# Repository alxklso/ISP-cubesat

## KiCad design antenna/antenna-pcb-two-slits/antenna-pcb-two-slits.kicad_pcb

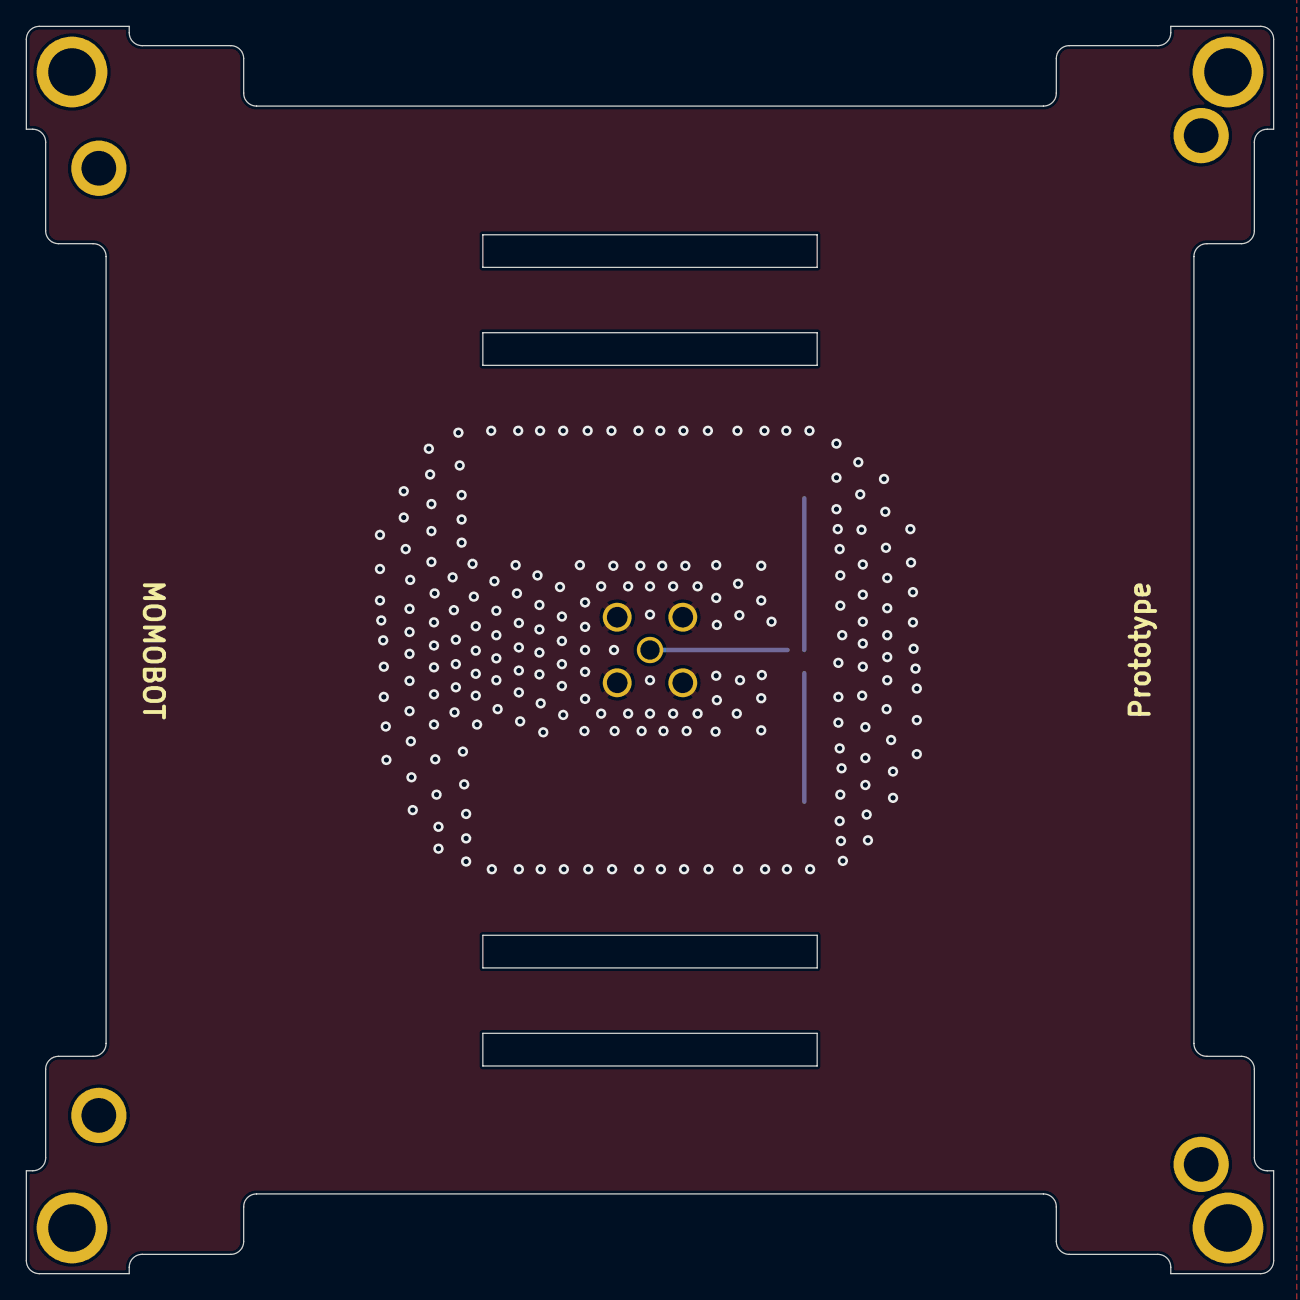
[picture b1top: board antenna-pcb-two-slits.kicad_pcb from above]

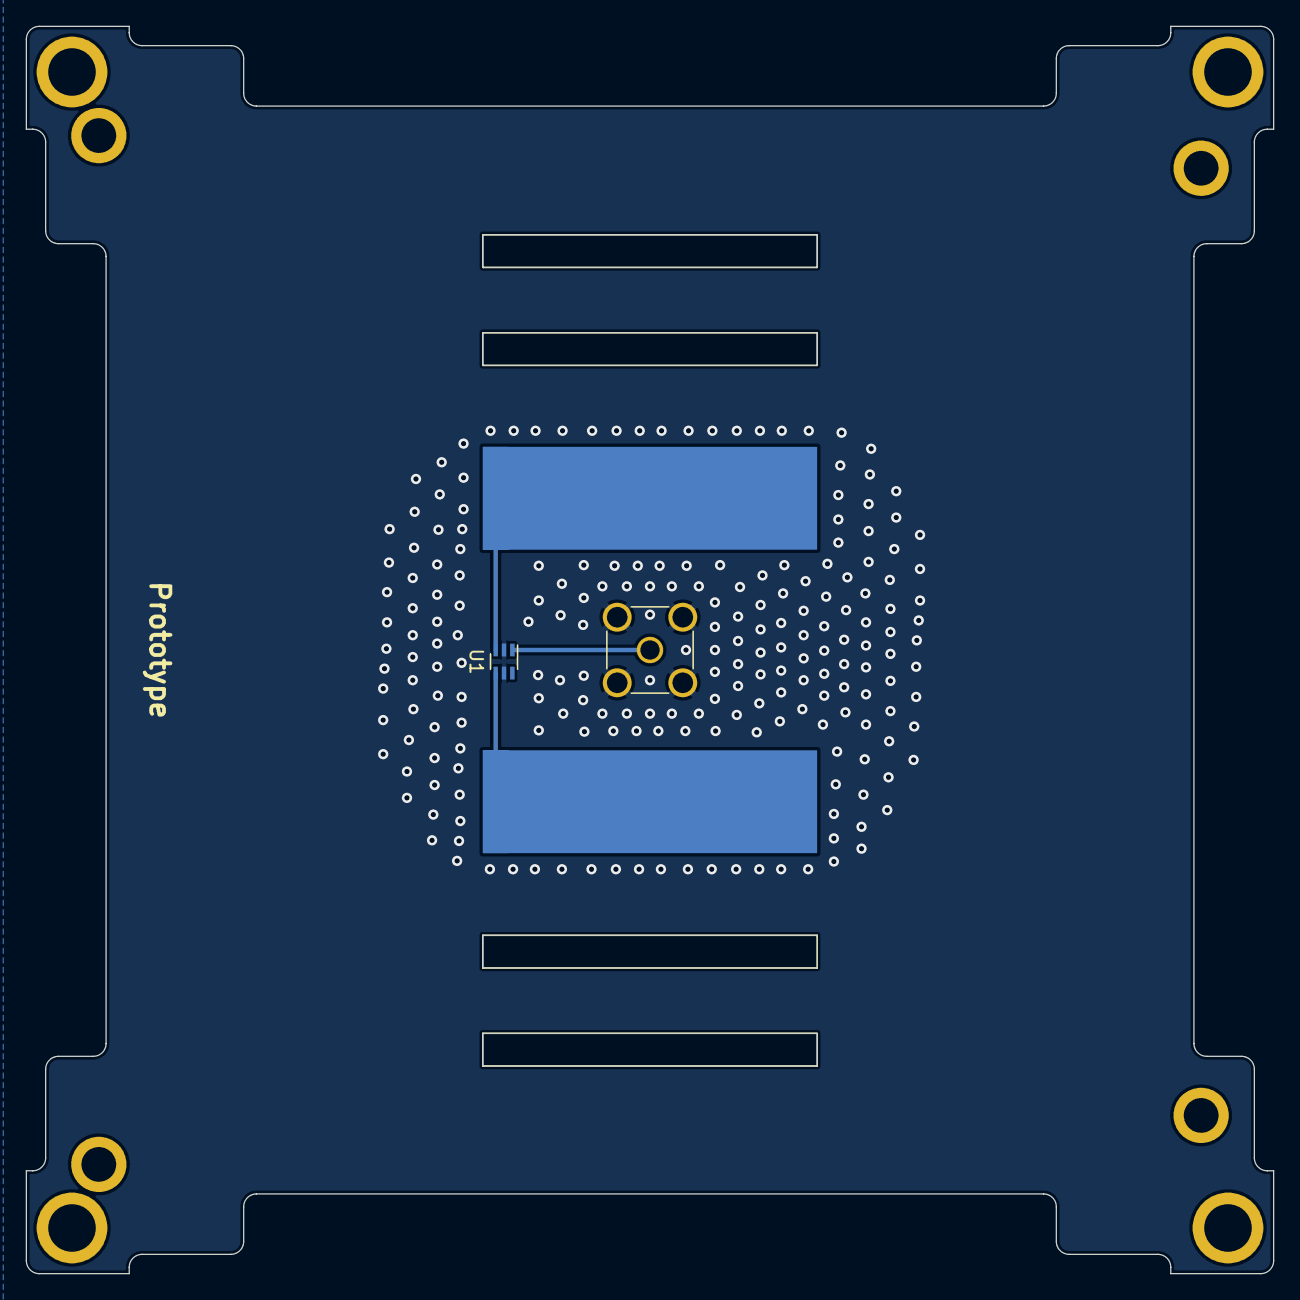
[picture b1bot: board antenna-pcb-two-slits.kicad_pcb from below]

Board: 2 copper layers, 97.0 x 97.0 mm, 11 parts (3 on the bottom side), 4 nets.

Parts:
AE1: Dipole_Antenna; Antenna_Pads_Two_Slits
H1, H2, H3, H4: MountingHole; MountingHole_3.7mm_Pad_Modified
H5, H6, H7, H8: MountingHole; MountingHole_2.7mm_M2.5_DIN965_Pad
J1: SMA Connector Male; SMA_Connector
U1: HHM1589D1; Balun_Johanson_5400BL15B050E

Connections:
GND: J1.2 (Ext), U1.2 (GND), U1.5 (GND)
unnamed: AE1.1, U1.3 (Balanced_Port)
unnamed: AE1.2, U1.4 (Balanced_Port)
unnamed: J1.1 (In), U1.1 (Balanced_Port)

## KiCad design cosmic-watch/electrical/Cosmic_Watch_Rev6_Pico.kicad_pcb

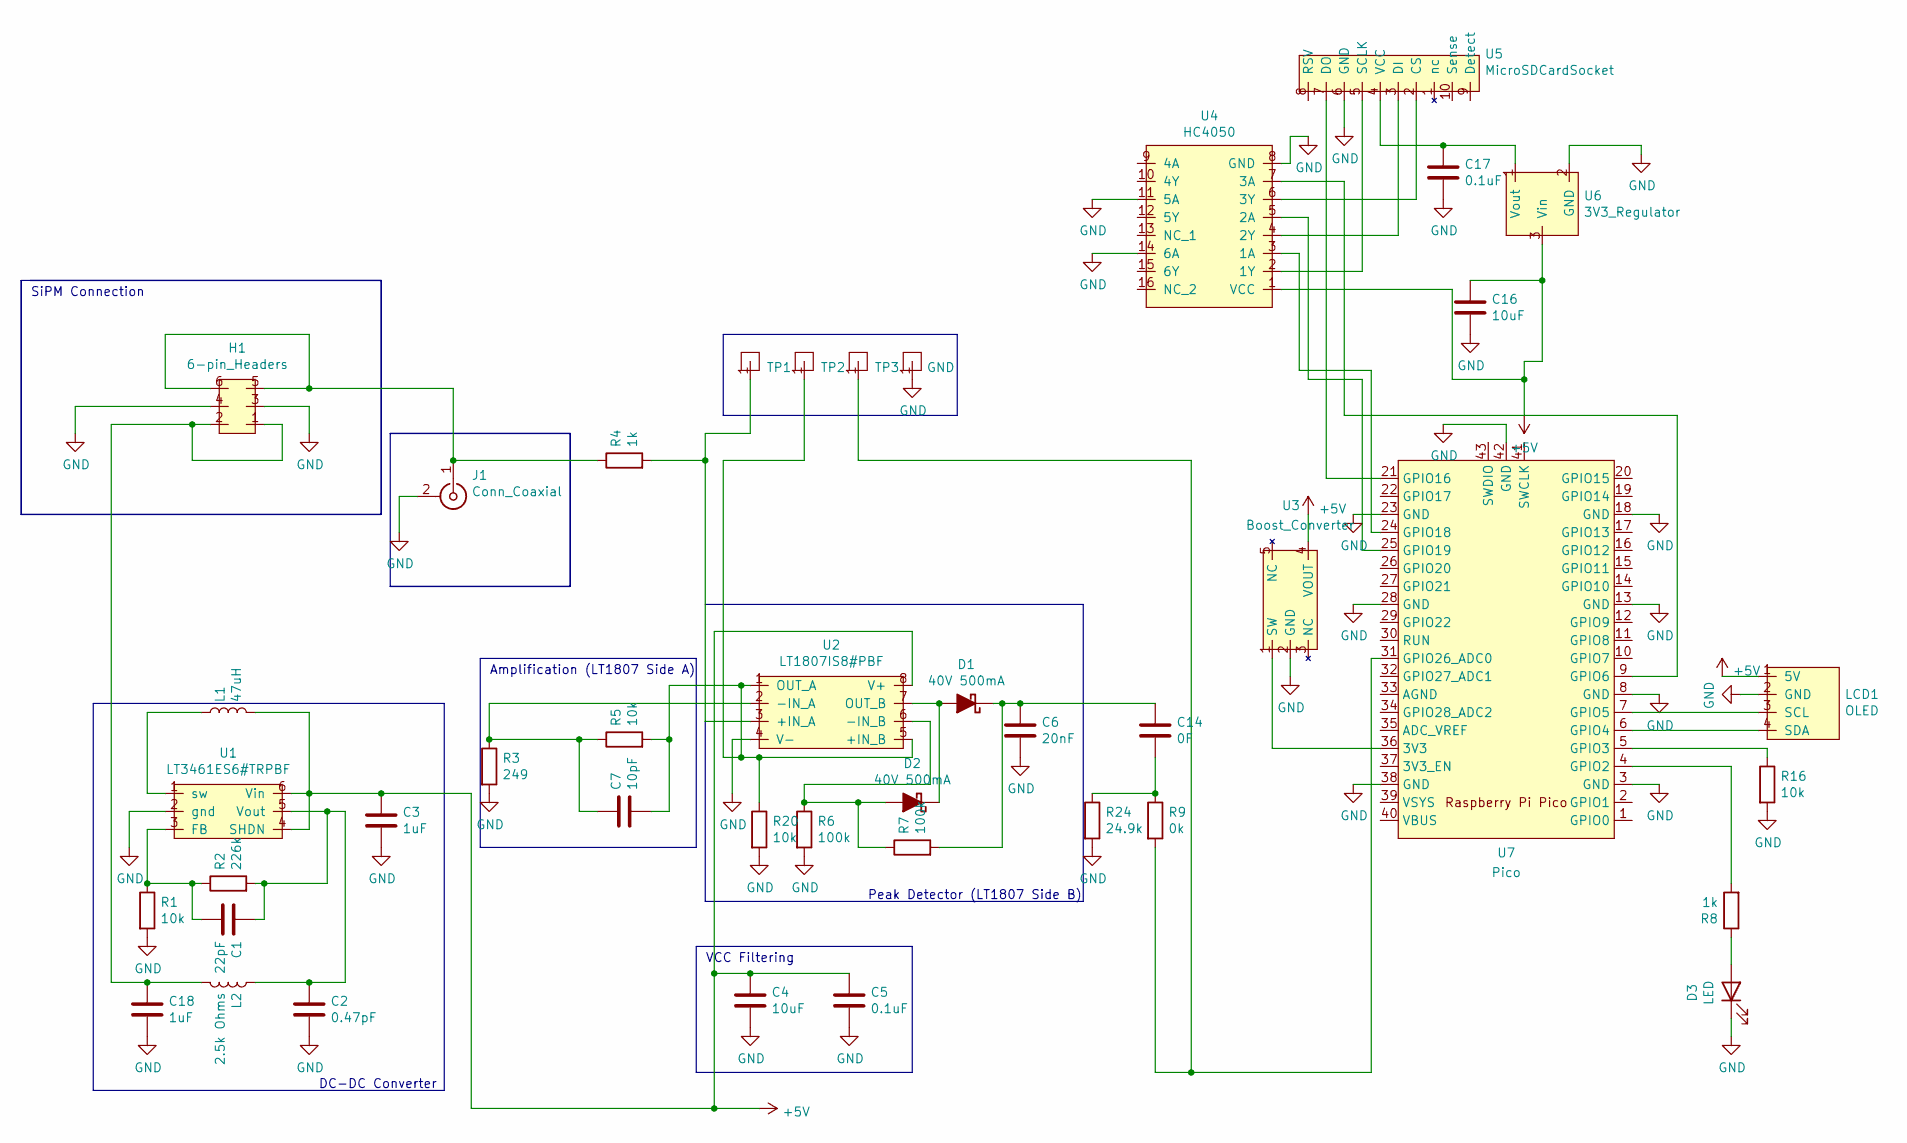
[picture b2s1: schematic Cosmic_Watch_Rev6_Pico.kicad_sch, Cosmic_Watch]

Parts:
C1: 22pF; C_0805_2012Metric_Pad1.18x1.45mm_HandSolder
C2: 0.47pF; C_0805_2012Metric_Pad1.18x1.45mm_HandSolder
C3, C18: 1uF; C_0805_2012Metric_Pad1.18x1.45mm_HandSolder
C4, C16: 10uF; C_0805_2012Metric_Pad1.18x1.45mm_HandSolder
C5, C17: 0.1uF; C_0805_2012Metric_Pad1.18x1.45mm_HandSolder
C6: 20nF; C_0805_2012Metric_Pad1.18x1.45mm_HandSolder
C7: 10pF; C_0805_2012Metric_Pad1.18x1.45mm_HandSolder
C14: 0F; C_0805_2012Metric_Pad1.18x1.45mm_HandSolder
D1, D2: 40V 500mA; D_SOD-123
D3: LED; LED_0805_2012Metric
H1: 6-pin_Headers; PinSocket_2x03_P2.54mm_Vertical
J1: Conn_Coaxial; BNC_Amphenol_B6252HB-NPP3G-50_Horizontal
L1: 47uH; L_1210_3225Metric_Pad1.42x2.65mm_HandSolder
L2: 2.5k Ohms; L_0805_2012Metric_Pad1.15x1.40mm_HandSolder
LCD1: OLED; 128x64OLED
R1, R5, R16, R20: 10k; R_0805_2012Metric_Pad1.20x1.40mm_HandSolder
R2: 226k; R_0805_2012Metric_Pad1.20x1.40mm_HandSolder
R3: 249; R_0805_2012Metric_Pad1.20x1.40mm_HandSolder
R4, R8: 1k; R_0805_2012Metric_Pad1.20x1.40mm_HandSolder
R6, R7: 100k; R_0805_2012Metric_Pad1.20x1.40mm_HandSolder
R9: 0k; R_0805_2012Metric_Pad1.20x1.40mm_HandSolder
R24: 24.9k; R_0805_2012Metric_Pad1.20x1.40mm_HandSolder
TP1, TP2, TP3: Test_Point1; TestPoint_THTPad_D3.0mm_Drill1.5mm
TP4: GND; TestPoint_THTPad_4.0x4.0mm_Drill2.0mm
U1: LT3461ES6#TRPBF; TSOT-23-6
U2: LT1807IS8#PBF; SOIC-8_3.9x4.9mm_P1.27mm
U3: Boost_Converter; SOT-23-5_HandSoldering
U4: HC4050; SOIC-HC4050
U5: MicroSDCardSocket; microSD_HC_Hirose_DM3AT-SF-PEJM5
U6: 3V3_Regulator; SOT-23
U7: Pico; Pico_No_THT

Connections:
GND: C2.2, C3.2, C4.2, C5.2, C6.2, C16.2, C17.2, C18.2, D3.1 (K), H1.3, H1.4, J1.2 (Ext), LCD1.2 (GND), R1.2, R3.2, R6.2, R16.2, R20.2, R24.2, TP4.1, U1.2 (gnd), U2.4 (V-), U3.2 (GND), U4.8 (GND), U4.11 (5A), U4.14 (6A), U5.6 (GND), U6.2 (GND), U7.3 (GND), U7.8 (GND), U7.13 (GND), U7.18 (GND), U7.23 (GND), U7.28 (GND), U7.38 (GND), U7.42 (GND)
unnamed: C1.1, C2.1, L2.1, R2.2, U1.5 (Vout)
unnamed: C1.2, R1.1, R2.1, U1.3 (FB)
unnamed: C7.1, R3.1, R5.1, U2.2 (-IN_A)
unnamed: C7.2, R5.2, R20.1, TP2.1 (TP1), U2.1 (OUT_A), U2.5 (+IN_B)
unnamed: C6.1, C14.1, D1.1 (K), R7.2
unnamed: C14.2, R9.1, R24.1
unnamed: C17.1, U5.4 (VCC), U6.1 (Vout)
unnamed: C18.1, H1.1, H1.2, L2.2
unnamed: D1.2 (A), D2.1 (K), U2.7 (OUT_B)
unnamed: D2.2 (A), R6.1, R7.1, U2.6 (-IN_B)
unnamed: D3.2 (A), R8.1
unnamed: H1.5, H1.6, J1.1 (In), R4.1
unnamed: L1.1, U1.1 (sw)
unnamed: LCD1.3 (SCL), U7.7 (GPIO5)
unnamed: LCD1.4 (SDA), U7.6 (GPIO4)
unnamed: R4.2, TP1.1 (TP1), U2.3 (+IN_A)
unnamed: R8.2, U7.4 (GPIO2)
unnamed: R9.2, TP3.1 (TP1), U7.31 (GPIO26_ADC0)
unnamed: R16.1, U7.5 (GPIO3)
unnamed: U3.1 (SW), U7.36 (3V3)
unnamed: U4.2 (1Y), U5.5 (SCLK)
unnamed: U4.3 (1A), U7.24 (GPIO18)
unnamed: U4.4 (2Y), U5.3 (DI)
unnamed: U4.5 (2A), U7.25 (GPIO19)
unnamed: U4.6 (3Y), U5.2 (CS)
unnamed: U5.7 (DO), U7.21 (GPIO16)

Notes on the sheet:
Peak Detector (LT1807 Side B)
SiPM Connection
VCC Filtering
Amplification (LT1807 Side A)
DC-DC Converter

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
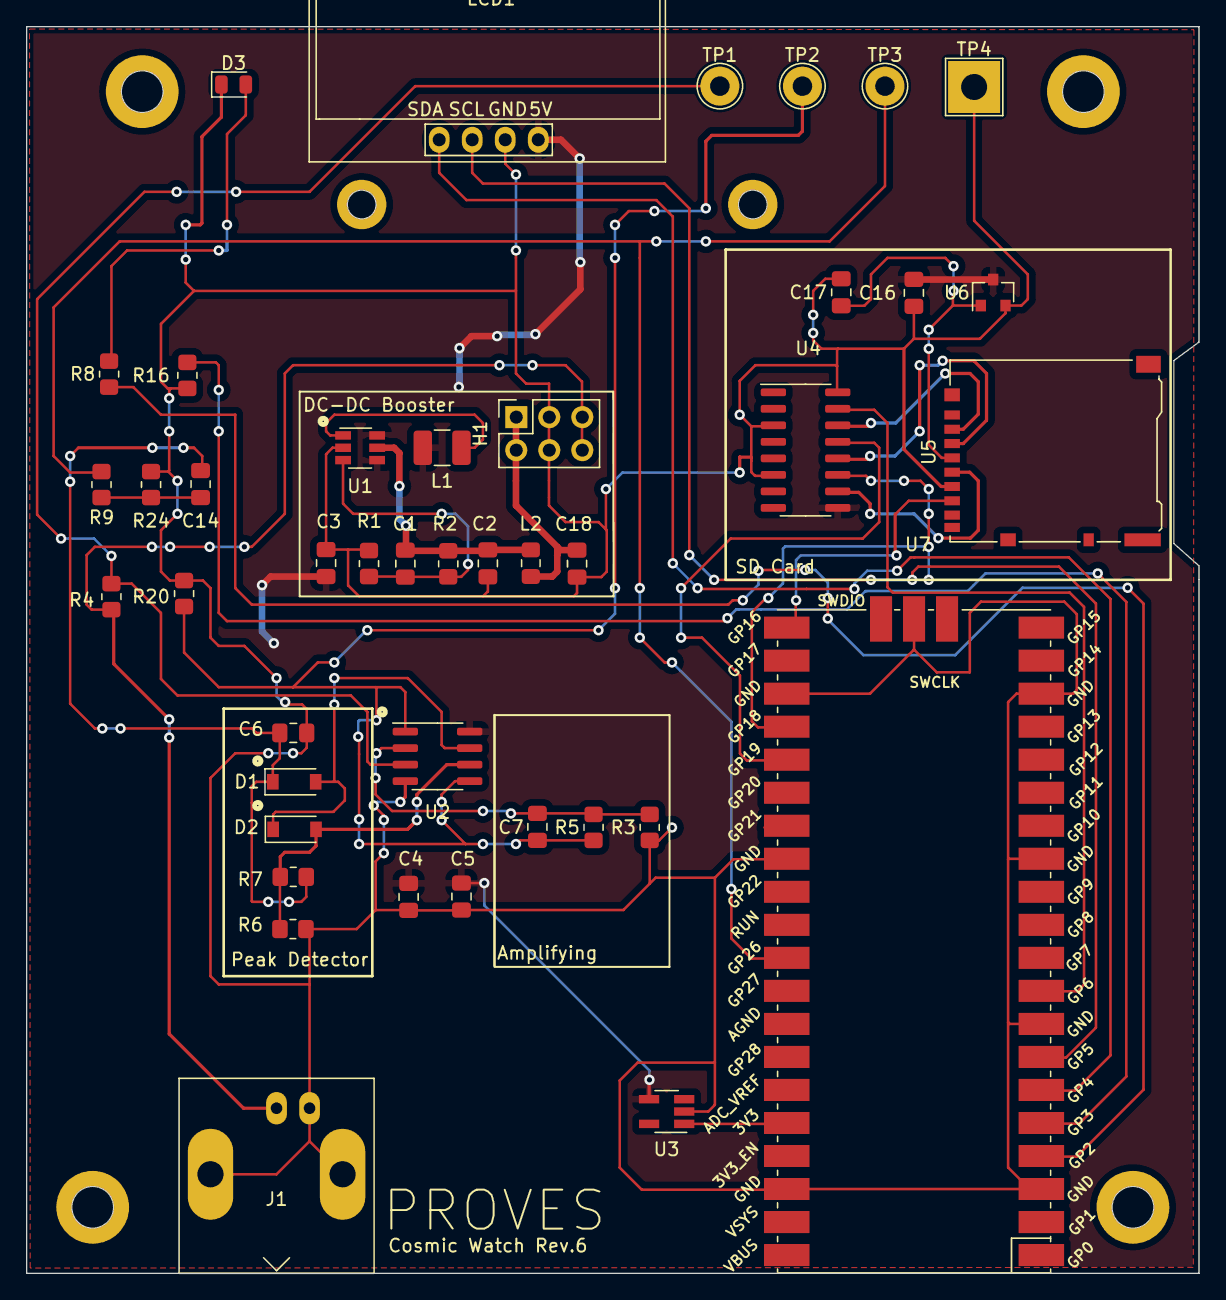
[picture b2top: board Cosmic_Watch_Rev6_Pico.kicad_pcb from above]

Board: 2 copper layers, 90.2 x 95.9 mm, 44 parts (0 on the bottom side), 29 nets.

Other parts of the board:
1, 1#2: MountingHole_2.2mm_M2_DIN965

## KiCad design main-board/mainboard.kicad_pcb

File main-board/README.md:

This is the folder that contains the PyCubed V5 mainboard files for the ISP 1U CubeSat mission. No modifications have been made to the  original PyCubed V5 mainboard design.

This folder contains:
- KiCad project files
- Schematic files 
- Gerbers (zip)
- PCB design files
- Bill of materials

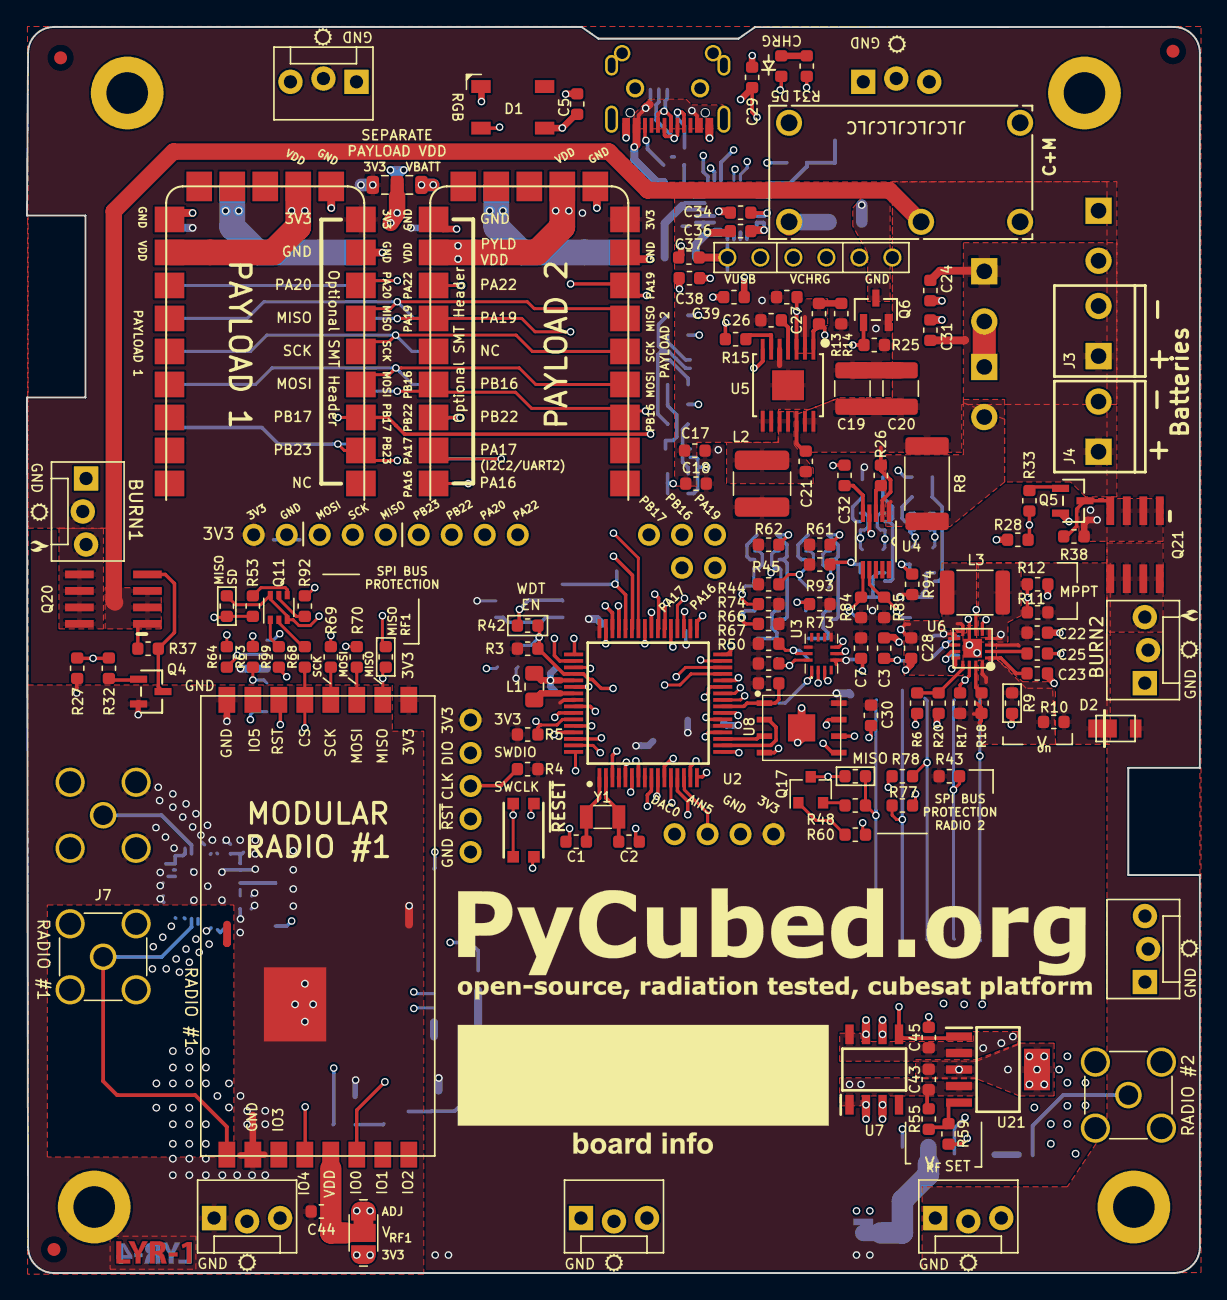
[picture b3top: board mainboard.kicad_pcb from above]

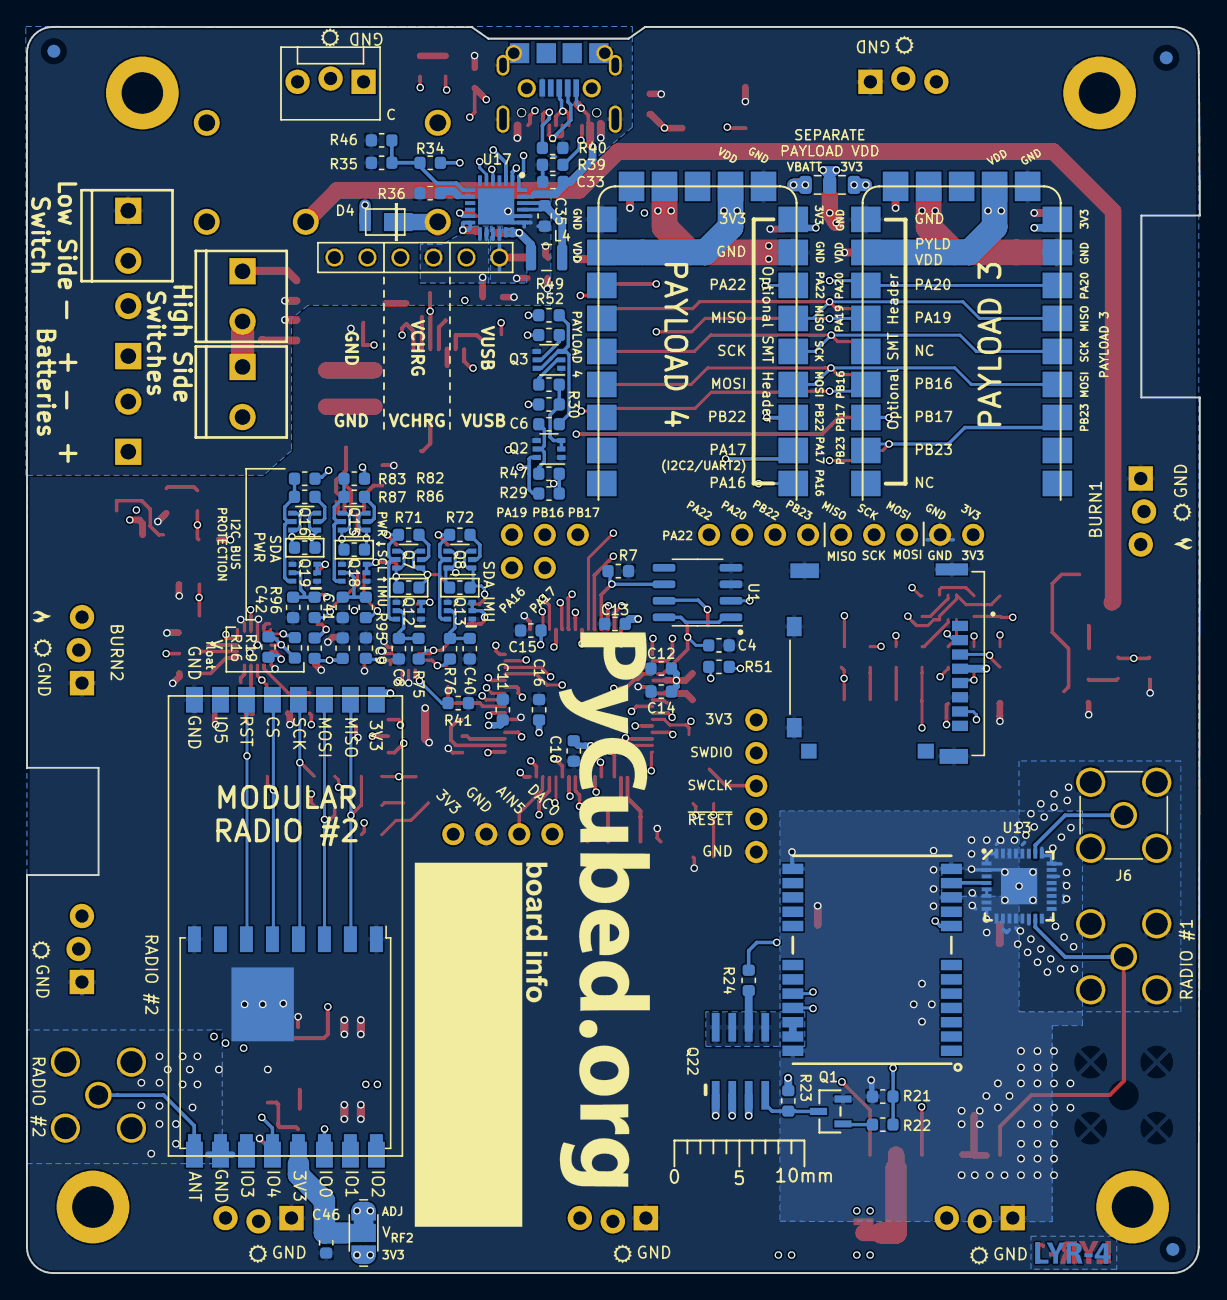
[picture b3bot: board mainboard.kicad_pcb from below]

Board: 4 copper layers, 90.3 x 95.9 mm, 229 parts (90 on the bottom side), 159 nets.

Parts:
C1, C2: 8pF; C_0603_1608Metric
C3, C5, C7, C9, C10, C11, C21, C24, C30, C45: 0.1uF; C_0603_1608Metric
C4, C12, C13, C15, C27, C33: 1uF; C_0603_1608Metric
C6, C14, C16, C22, C35, C39, C43, C44, C46: 10uF; C_0603_1608Metric
C8, C40, C41, C42: 10nF; C_0603_1608Metric
C17, C18, C28, C31, C37, C38: 22uF; C_0603_1608Metric
C19, C20: 100uF; C_1210_3225Metric
C23: 2.2uF; C_0603_1608Metric
C25: 22nF; C_0603_1608Metric
C26, C32: 3.3nF; C_0603_1608Metric
C29, C34: 4.7uF; C_0603_1608Metric
C36: 47nF; C_0603_1608Metric
D1: WS2812B; LED_WS2812B_PLCC4_5.0x5.0mm_P3.2mm
D2, D4: DFLS130L; PWRDI-123
D5: GREEN LED; LED_0603_1608Metric
H1, H2, H3, H4: MountingHole_Pad; MountingHole_3.2mm_M3_DIN965_Pad
J1: 503182-1852; MOLEX_503182-1852
J2: Conn_01x05; PinHeader_1x05_P2.54mm_Vertical
J3, J4, J16, J17, J18: 1985807; SCREWTERMINAL-3.5MM-2_LOCK
J6, J7, J12: Amphenol_901-144; SMA_Amphenol_901-144_Vertical
J8: Conn_01x09; PinHeader_1x09_P2.54mm_Vertical
J9: Conn_01x03; PinHeader_1x03_P2.54mm_Vertical
J10: Conn_01x04; PinHeader_1x04_P2.54mm_Vertical
J11: 10118194-0001LF
J13: USB_C_Receptacle_USB2.0; USB_C_Receptacle_XKB_U262-161N-4BVC11
J14: Conn_01x06; PinHeader_1x06_P2.54mm_Vertical
J15: Conn_01x02; PinHeader_CUSTOM3
JP6, JP7: Jumper_3_Bridged12; SolderJumper-3_P1.3mm_Bridged12_RoundedPad1.0x1.5mm
JP8, JP9, JP10, JP11, JP12, JP13, JP14, JP15: Conn_01x03; MOLEX-1X3_LOCK
L1: 10uH; L_0805_2012Metric_Pad1.15x1.40mm_HandSolder
L2: 3.3uH; L_2141
L3: 33uH; L_1812_4532Metric
L4: 1uH; L_2510
Q1, Q4, Q5: IRLML2803; SOT-23
Q2, Q3, Q7, Q8, Q15, Q16: MBT2222ADW1T1; SOT-363_SC-70-6
Q6: MMBT2222AT; SOT-23
Q11: MMDT2907; SOT-363_SC-70-6
Q12, Q13, Q18, Q19: BSS138DWQ-7
Q17: MMBT2907; SOT-23
Q20, Q21, Q22: NDS8434
R1: 316K; R_0603_1608Metric
R2: 110K; R_0603_1608Metric
R3, R4, R5, R7, R21, R24, R25, R27, R28, R31, R41, R42, R43, R44, R45, R46, R50, R51, R52, R55, R61, R62, R66, R67, R82, R83, R84, R85: 10K; R_0603_1608Metric
R6, R22, R32, R33, R60, R68, R92: 4.7K; R_0603_1608Metric
R8: 0.1; R_2512_6332Metric
R9: 107K; R_0603_1608Metric
R10, R48, R53, R97, R98, R99, R101, R104, R107, R108, R109: 0; R_0603_1608Metric
R11: 787K; R_0603_1608Metric
R12: 121K; R_0603_1608Metric
R13, R29: 73.2K; R_0603_1608Metric
R14: 22.1K; R_0603_1608Metric
R15, R30, R49, R73, R74, R93, R94: 100K; R_0603_1608Metric
R16: 845K; R_0603_1608Metric
R17, R18, R37, R38: 100k; R_0603_1608Metric
R19: 2.1M; R_0603_1608Metric
R20: 3.01K; R_0603_1608Metric
R23, R59: 3.3K; R_0603_1608Metric
R26, R63, R64, R69, R70, R77, R78: 1K; R_0603_1608Metric
R34: 5.23K; R_0603_1608Metric
R35: 30.1K; R_0603_1608Metric
R36: 3.16K; R_0603_1608Metric
R39, R40: 5.1K; R_0603_1608Metric
R47, R75, R76, R95, R96: 200K; R_0603_1608Metric
R54, R56, R57, R58: 0; R_0805_2012Metric
R71, R72, R86, R87: 680; R_0603_1608Metric
R110: 20K; R_0603_1608Metric
REF1B, REF1T, REF2B, REF2T, REF3B, REF3T: Fiducial_1mm_Mask2mm
SW1: KMR231NG LFS; BTN_KMR2_4.6X2.8
U1: MAX706RESA; SO-8_3.9x4.9mm_P1.27mm
U2: ATSAMD51J19A-AU; QFP50P1200X1200X120-64N
U3: BMX160
U4: ADM1176-1ARMZ-R7
U5: TPS54226PWPRPWP14_2P31X2P46-L; PWP14_2P31X2P46-L
U6: LTC4121; QFN-16-PAD
U7: KF50BD-TR; SOIC127P600X175-8N
U8: MR25H40MDF; SON127P600X500X90-9N
U9, U10, U11, U12: XTB-40; XTB40_payload
U13: EP2W+; QFN32-5X5MM
U14: S1216V8; S1216_24PIN_PACKAGE
U15: RFM9xBreakout; HOPERF_RFM9XW_SMD
U16: PE014006; RELAY_PE014006
U17: BQ25883RGER; QFN50P400X400X100-25N-D
U21: TPS7A4501DCQT
U23, U24: RFM98PW; RFM95PW
Y1: 32.768kHz; Crystal_SMD_3215-2Pin_3.2x1.5mm

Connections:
3.3V: C5.1, C7.1, C9.2, C10.1, C11.1, C13.1, C15.1, C16.1, C17.2, C18.2, C30.1, D1.1, J1.4, J2.1, J8.1, J10.4, JP6.3, JP7.3, L2.2, Q22.1, Q22.2, Q22.3, R3.1, R4.1, R5.1, R13.2, R17.2, R18.2, R23.1, R43.1, R44.1, R45.1, R50.2, R51.2, R54.1, R57.1, R61.1, R62.1, R66.1, R67.1, R73.1, R74.1, R82.1, R83.1, R84.1, R85.1, R93.1, R94.1, U1.2, U2.4, U2.8, U2.21, U2.34, U2.48, U2.56, U3.5, U3.8, U3.12, U5.1, U8.8, U9.9, U10.9, U11.9, U12.9, U23.9, U24.9
/Avionics/BATTERY: C3.1, R1.2, R2.2, U2.15
/Avionics/XTAL1: C1.1, U2.1, Y1.1
/Avionics/XTAL2: C2.1, U2.2, Y1.2
/Burn Wires/VBURN1: JP11.3, Q20.5, Q20.6, Q20.7, Q20.8
/Burn Wires/VBURN2: JP12.3, Q21.5, Q21.6, Q21.7, Q21.8
/Burn Wires/VBURN_A_IN: Q20.1, Q20.2, Q20.3, Q21.1, Q21.2, Q21.3, R37.2, R38.2, U16.11
/Power/3V3_EN: Q2.6, R29.2, U5.7
/Power/REGN: C34.1, R31.2, U17.11
/Power/VCHRG_IN: C22.1, D2.C, R10.2, R11.2, U6.P$3
/Power/V_RF: C43.2, JP6.1, JP7.1, R55.1, U7.1, U21.4
/RF and GPS/PYLD12_VDD: R54.2, R56.1, U10.11, U10.16, U12.11, U12.16
/RF and GPS/PYLD34_VDD: R57.2, R58.1, U9.11, U9.16, U11.11, U11.16
/RF and GPS/RF2_ANT: J12.1, U15.9, U24.1
/RF and GPS/RF_IN: U13.4, U14.11
AIN5: J10.2, U2.14
BURN_RELAY_A: Q6.1, R25.1, U2.28
DAC0: J10.1, U2.3
ENAB_BURN1: R27.1, R32.2, U2.60
ENAB_BURN2: R28.1, R33.2, U2.32
ENAB_GPS: R21.1, R22.1, U2.62
ENAB_RF: U2.13, U7.5, U21.1
FLASH_CS: R50.1, U2.24, U8.1
FLASH_IO2: U2.19, U8.3
FLASH_IO3: U2.20, U8.7
FLASH_MISO: U2.18, U8.2
FLASH_MOSI: U2.17, U8.5
FLASH_SCK: U2.23, U8.6
GND: C1.2, C2.2, C3.2, C4.1, C5.2, C7.2, C8.2, C9.1, C10.2, C11.2, C12.1, C13.2, C14.2, C15.2, C16.2, C17.1, C18.1, C19.2, C20.2, C22.2, C23.2, C26.2, C27.2, C28.2, C30.2, C32.1, C40.2, C41.2, C42.2, C43.1, C44.1, C45.1, C46.1, D1.3, H1.1, H2.1, H3.1, H4.1, J1.6, J1.P1, J1.P2, J1.P3, J1.P4, J1.P5, J2.5, J6.2, J7.2, J8.2, J10.3, J12.2, J14.5, J18.2, JP8.1, JP9.1, JP10.1, JP11.1, JP12.1, JP13.1, JP14.1, JP15.1, Q1.2, Q2.1, Q2.4, Q3.1, Q3.4, Q4.2, Q5.2, Q6.2, Q12.1, Q12.4, Q13.1, Q13.4, Q18.1, Q18.4, Q19.1, Q19.4, R2.1, R7.1, R9.2, R12.1, R14.1, R20.1, R21.2, R25.2, R27.2, R28.2, R41.2, R59.2, SW1.B, SW1.B', U1.3, U1.4, U2.7, U2.22, U2.33, U2.47, U2.54, U3.2, U3.3, U3.6, U3.7, U4.4, U5.5, U5.8, U5.9, U5.15, U6.P$5, U6.P$7, U6.P$12, U6.P$17, U7.2, U7.3, U7.6, U7.7, U8.4, U8.9, U9.8, U9.10, U9.15, U10.8, U10.10, U10.15, U11.8, U11.10, U11.15, U12.8, U12.10, U12.15, U13.1, U13.2, U13.3, U13.5, U13.6, U13.7, U13.8, U13.9, U13.10, U13.11, U13.12, U13.13, U13.14, U13.16, U13.17, U13.18, U13.19, U13.20, U13.21, U13.22, U13.23, U13.24, U13.25, U13.27, U13.28, U13.29, U13.30, U13.31, U13.32, U13.EP, U14.10, U14.12, U14.13, U14.24, U15.1, U15.8, U15.10, U16.12, U21.3, U21.6, U23.2, U23.16, U23.17, U24.2, U24.16, U24.17
GNDREF: C24.2, C29.2, C31.2, C33.1, C34.2, C35.1, C37.1, C38.1, C39.1, J3.2, J4.2, J11.5, J11.8, J11.9, J13.A1, J13.A12, J13.S1, J14.6, J18.1, R35.1, R36.1, R39.1, R40.1, R46.1, U17.19, U17.20, U17.25
GPS_PWR_IN: Q22.5, Q22.6, Q22.7, Q22.8, R24.2, U14.22, U14.23
L1_PROG: R6.1, R20.2, U6.P$13
MISO: J8.5, Q11.3, Q11.6, Q17.3, R101.2, R104.2, R107.2, U2.31, U9.6, U10.6, U11.6, U12.6
MISO_RF1: R99.2, R101.1, U23.10
MISO_RF2: R48.2, R107.1, U15.2, U24.10
MISO_SD: J1.7, R53.2, R104.1
MOSI: J8.3, R64.2, R70.1, R77.2, U2.29, U9.4, U10.4, U11.4, U12.4
MOSI_RF1: R70.2, U23.11
MOSI_RF2: R77.1, U15.3, U24.11
MOSI_SD: J1.3, R64.1
unnamed: C6.1, Q3.3, Q3.6, R49.2
unnamed: C6.2, Q2.5, R47.2
unnamed: C8.1, Q12.5, R75.2
unnamed: C12.2, C14.1, L1.1, U2.53
unnamed: C21.1, L2.1, U5.10, U5.11
unnamed: C21.2, U5.12
unnamed: C23.1, U6.P$1
unnamed: C25.1, U6.P$2
unnamed: C25.2, L3.2, U6.P$4
unnamed: C26.1, U5.4
unnamed: C27.1, R15.2, U5.3
unnamed: C32.2, U4.5
unnamed: C35.2, L4.1, U17.21, U17.22
unnamed: C36.1, L4.2, U17.17, U17.18
unnamed: C36.2, U17.12
unnamed: C37.2, C38.2, J14.1, U17.15, U17.16
unnamed: C39.2, J14.3, U17.13, U17.14
unnamed: C40.1, Q13.5, R76.2
unnamed: C41.1, Q18.5, R95.2
unnamed: C42.1, Q19.5, R96.2
unnamed: D1.4, U2.42
unnamed: D4.A, Q6.3, U16.5
unnamed: D5.2, R31.1
unnamed: J6.1, U13.26
unnamed: J16.2, J17.1
unnamed: L1.2, U2.55
unnamed: L3.1, U6.P$8
unnamed: Q1.1, R22.2
unnamed: Q1.3, Q22.4, R23.2
unnamed: Q2.2, Q2.3, R30.2, R110.2
unnamed: Q3.2, R110.1
unnamed: Q3.5, R52.1
unnamed: Q4.1, R32.1
unnamed: Q5.1, R33.1
unnamed: Q7.2, R71.1
unnamed: Q8.2, R72.1
unnamed: Q11.1, R99.1
unnamed: Q11.2, R68.1
unnamed: Q11.4, R53.1
unnamed: Q11.5, R92.1
unnamed: Q12.2, Q12.3, R73.2
unnamed: Q7.5, Q12.6, R61.2, R71.2
unnamed: Q13.2, Q13.3, R74.2
unnamed: Q8.5, Q13.6, R62.2, R72.2
unnamed: Q15.2, R86.1
unnamed: Q15.5, Q18.6, R82.2, R86.2
unnamed: Q16.2, R87.1
unnamed: Q16.5, Q19.6, R83.2, R87.2
unnamed: Q17.1, R60.1
unnamed: Q17.2, R48.1
unnamed: Q18.2, Q18.3, R93.2
unnamed: Q19.2, Q19.3, R94.2
unnamed: Q4.3, Q20.4, R37.1
unnamed: Q5.3, Q21.4, R38.1
unnamed: R6.2, U2.16
unnamed: R9.1, R10.1, U6.P$16
unnamed: R11.1, R12.2, U6.P$6
unnamed: R13.1, R14.2, U5.2
unnamed: R15.1, U5.6
unnamed: R16.1, U6.P$11
unnamed: R16.2, R19.2, U6.P$10
unnamed: R18.1, U6.P$15
unnamed: R24.1, U14.8
unnamed: R26.2, U4.3
unnamed: R36.2, U17.8
unnamed: R41.1, U3.1
unnamed: R42.2, U1.7
unnamed: R55.2, R59.1, U21.5
unnamed: U1.1, U1.8
PA16: J15.2, U2.35, U11.1, U12.23
PA17: J15.1, U2.36, U11.2, U12.22
PA19: J9.3, U2.38, U9.18, U12.7, U12.18
PA20: J8.8, U2.41, U9.7, U9.17, U10.7
PA22: J8.9, U2.43, U11.7, U12.17
PB16: J9.2, U2.39, U9.20, U12.3, U12.20
PB17: J9.1, U2.40, U9.21, U10.3
PB22: J8.7, U2.49, U11.3, U12.21
PB23: J8.6, U2.50, U9.3, U9.22, U10.2
RF1_ANT: J7.1, U23.1
RF1_CS: R5.2, R68.2, U2.59, U23.13
RF1_IO0: U2.6, U23.6
RF1_IO4: U2.5, U23.4
RF1_RST: U2.61, U23.14
RF2_CS: R43.2, R60.2, U2.12, U15.5, U24.13
RF2_IO0: U2.9, U15.14, U24.6
RF2_IO4: U2.10, U15.12, U24.4
RF2_RST: U2.27, U15.6, U24.14
RX: U2.64, U14.20
SCK: J8.4, R63.2, R69.2, R78.2, U2.30, U9.5, U10.5, U11.5, U12.5
SCK_RF1: R69.1, U23.12
SCK_RF2: R78.1, U15.4, U24.12
SCK_SD: J1.5, R63.1
SCL: Q7.1, Q7.3, Q15.1, Q15.3, R45.2, R97.2, R108.2, U2.26
SCL_IMU: Q7.4, Q7.6, R66.2, R75.1, R97.1, U3.13
SCL_PWR: Q15.4, Q15.6, R84.2, R95.1, R108.1, U4.6, U17.5
SDA: Q8.1, Q8.3, Q16.1, Q16.3, R44.2, R98.2, R109.2, U2.25
SDA_IMU: Q8.4, Q8.6, R67.2, R76.1, R98.1, U3.14
SDA_PWR: Q16.4, Q16.6, R85.2, R96.1, R109.1, U4.7, U17.4
SD_CS: J1.2, R51.1, R92.2, U2.51
STAT: D5.1, U17.2
SWCLK: J2.3, R4.2, U2.57
SWDIO: J2.2, U2.58
THM: R34.2, R35.2, R46.2, U17.7
TX: U2.63, U14.21
USB_CC1: J13.A5, R40.2
USB_CC2: J13.B5, R39.2
USB_D+: J11.3, J13.A6, J13.B6, U2.46, U17.24
USB_D-: J11.2, J13.A7, J13.B7, U2.45, U17.1
VBATT: C19.1, C20.1, C28.1, C45.2, D4.C, J14.2, R1.1, R8.1, R19.1, R26.1, R29.1, R30.1, R47.1, R49.1, R56.2, R58.2, U4.2, U5.13, U5.14, U6.P$9, U7.8, U16.1, U16.14, U21.2
VBATT_SENSE: J17.2, R8.2, U4.1
VBUS_IN: C29.1, C33.2, J11.1, J13.A4, J13.A9, R34.1, U17.23
VBUS_RESET: R52.2, U2.37
VCC_RF1: C44.2, JP6.2, U23.5
VCC_RF2: C46.2, JP7.2, U15.13, U24.5
VCHRG: C24.1, C31.1, J3.1, J4.1, J14.4, J16.1
VSOLAR: D2.A, JP8.2, JP9.2, JP10.2, JP11.2, JP12.2, JP13.2, JP14.2, JP15.2
WDT_WDI: R7.2, U1.6, U2.44
~CHRG: R17.1, U2.11, U6.P$14
~RESET: C4.2, J2.4, R3.2, R42.1, SW1.A, SW1.A', U2.52

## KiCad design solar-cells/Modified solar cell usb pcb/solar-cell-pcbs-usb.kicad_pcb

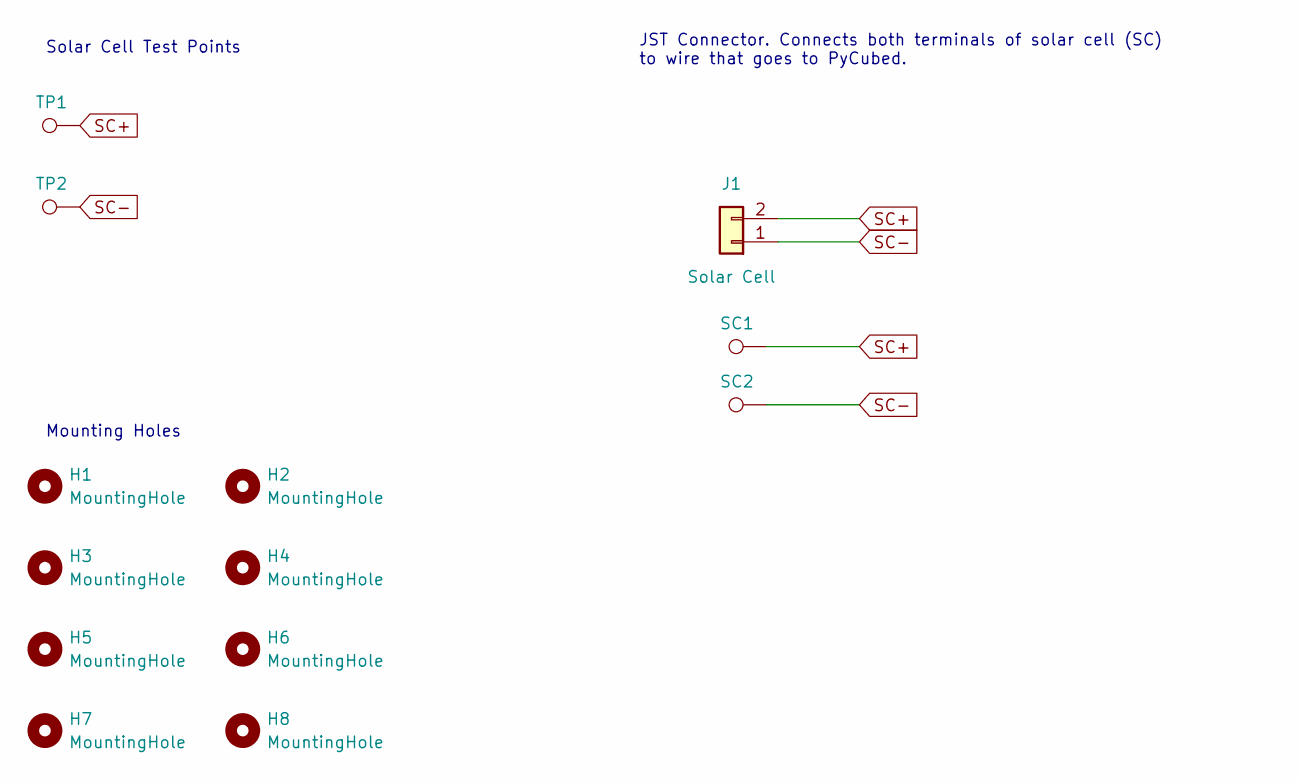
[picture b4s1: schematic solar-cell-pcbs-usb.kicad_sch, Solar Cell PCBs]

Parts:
H1, H2, H3, H4, H5, H6, H7, H8: MountingHole; MountingHole_3.2mm_M3_DIN965_Pad
J1: Solar Cell; 2053380002
SC1: SC+; TestPoint_THTPad_D3.0mm_Drill1.5mm
SC2: SC-; TestPoint_THTPad_D3.0mm_Drill1.5mm
TP1: SC+; TestPoint_Loop_D1.80mm_Drill1.0mm_Beaded
TP2: SC-; TestPoint_Loop_D1.80mm_Drill1.0mm_Beaded

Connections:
SC+: J1.2, SC1.1, TP1.1
SC-: J1.1, SC2.1, TP2.1

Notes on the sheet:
Solar Cell Test Points
Mounting Holes
JST Connector. Connects both terminals of solar cell (SC) to wire that goes to PyCubed.

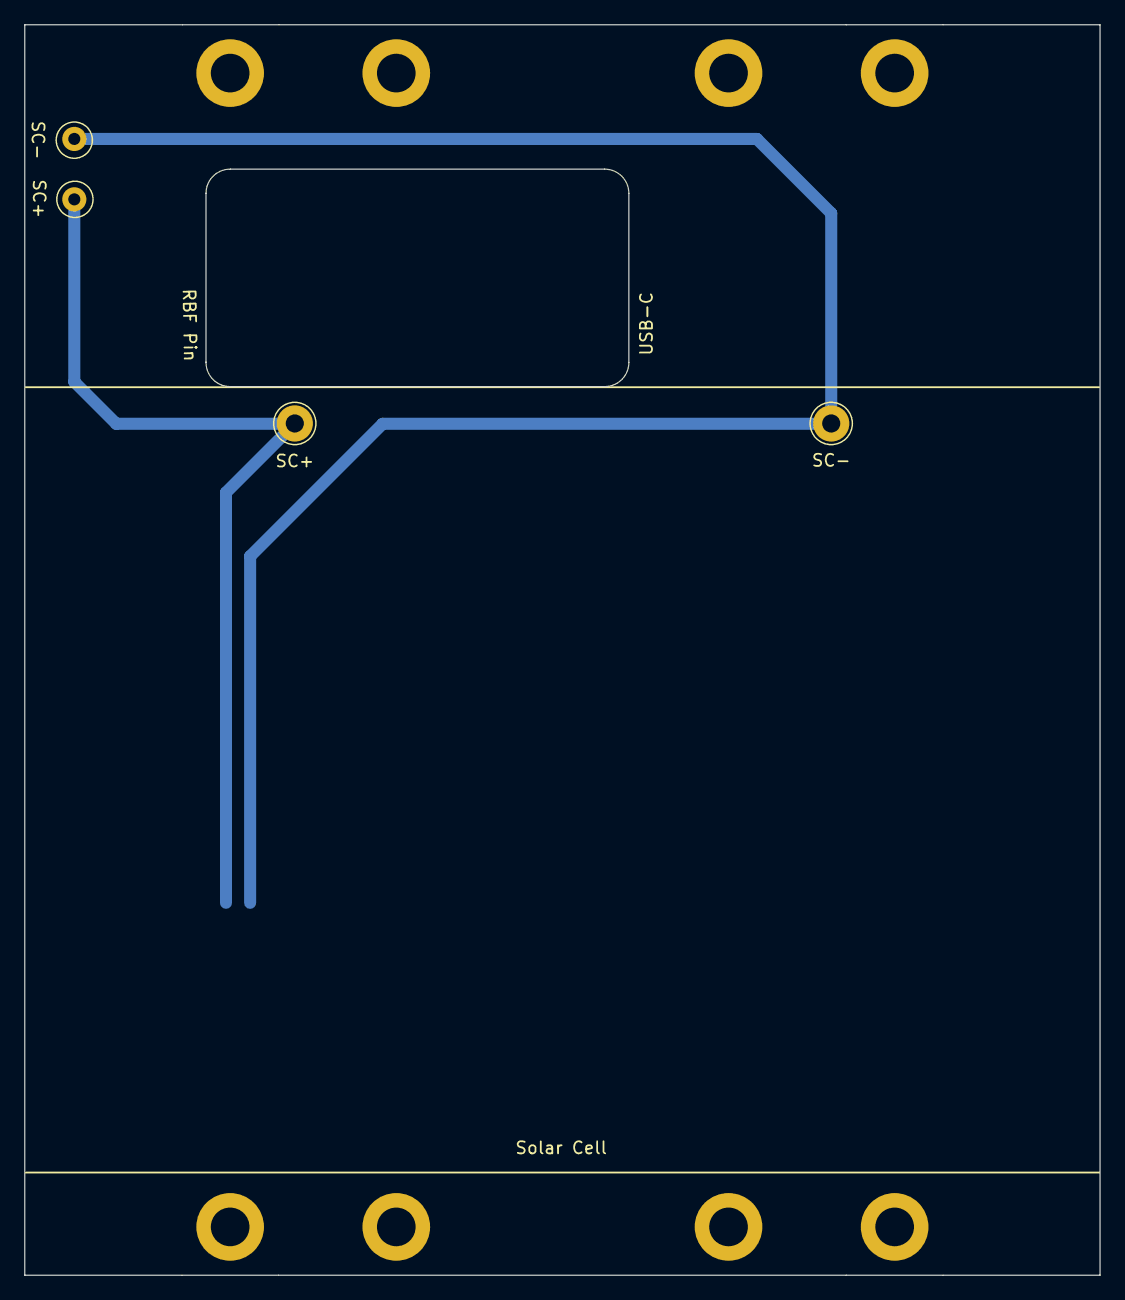
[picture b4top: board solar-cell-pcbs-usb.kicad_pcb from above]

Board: 2 copper layers, 89.0 x 103.5 mm, 13 parts (1 on the bottom side), 2 nets.

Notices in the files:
parts and their libraries:
Copyright 2016 Accelerated Designs. All rights reserved.
Copyright 2021 Accelerated Designs. All rights reserved.
